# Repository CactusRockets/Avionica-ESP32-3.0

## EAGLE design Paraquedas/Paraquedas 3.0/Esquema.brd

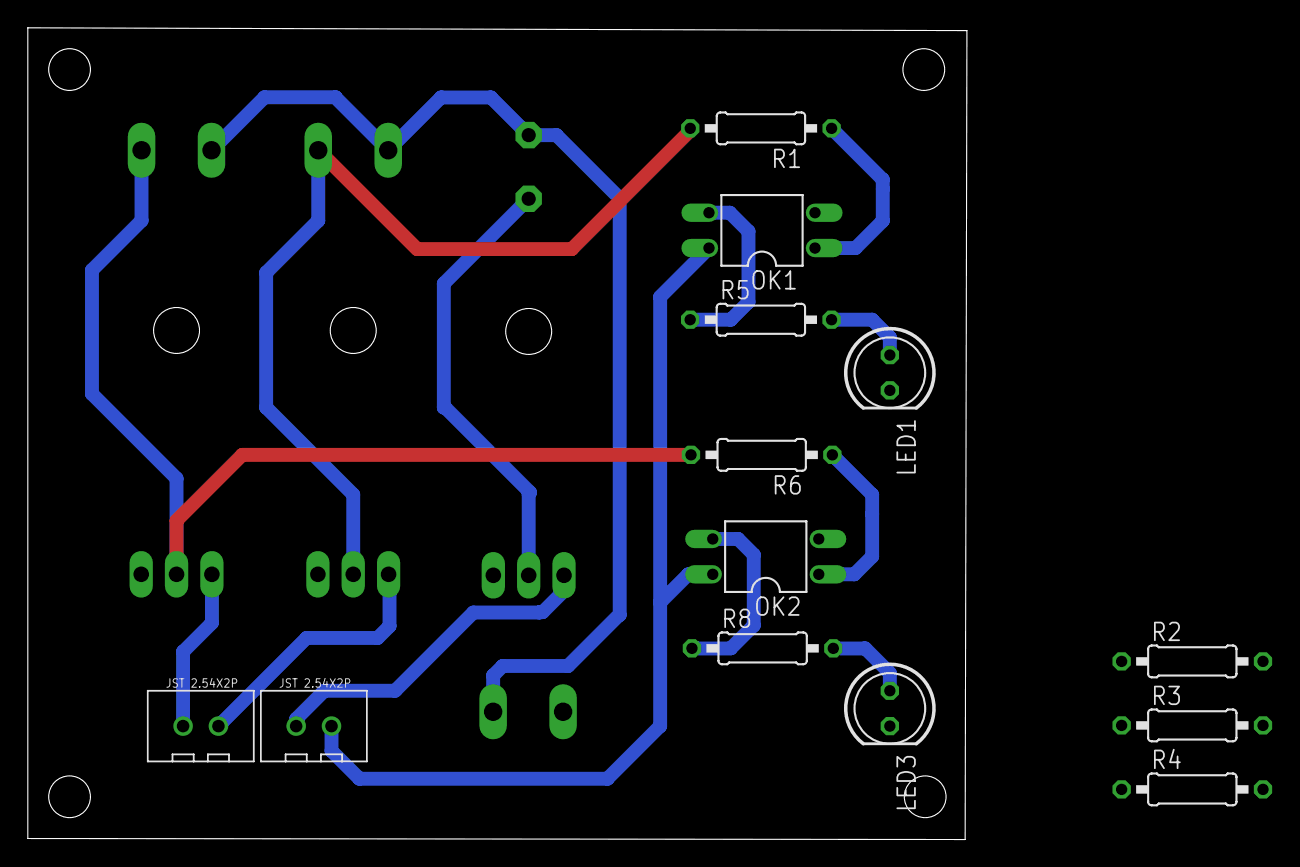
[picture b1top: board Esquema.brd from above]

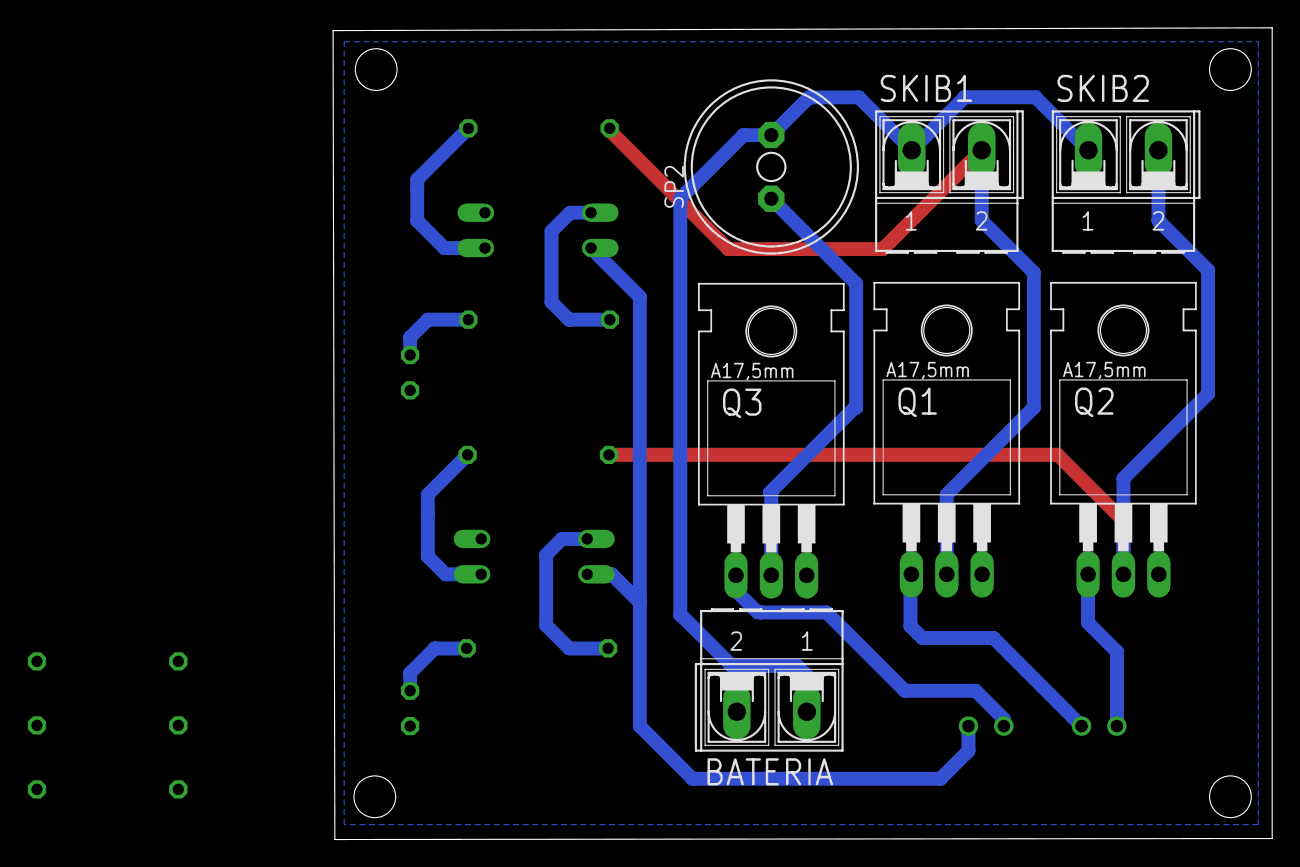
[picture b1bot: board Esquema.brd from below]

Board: 2 copper layers, 67.5 x 58.3 mm, 20 parts (7 on the bottom side), 15 nets.

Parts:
BATERIA: AK500/2-H
LED1, LED3: 5mm; LED5MM
OK1, OK2: PC817; DIL04
Q1, Q2, Q3: IRF540; TO220
R1, R5, R8: 220; 0207/10
R2, R3, R4, R6: 1k; 0207/10
SKIB1, SKIB2: AK500/2-H
SP2: AL11P
U$1, U$2: JST2.54X2P; JST2.54X2P_FOOTPRINT

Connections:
3.3V: OK1.4, OK2.4, U$1.2
BUZZER: Q3.1, U$1.1
GND: BATERIA.2, LED1.K, LED3.K, OK1.2, OK2.2, Q1.3, Q2.3, Q3.3
unnamed: Q3.2, SP2.-
unnamed: LED3.A, R8.2
unnamed: OK1.1, R1.1
unnamed: OK2.1, R6.1
unnamed: LED1.A, R5.2
SINAL_SKIB1: OK1.3, R5.1
SINAL_SKIB2: OK2.3, R8.1
SKIB1: Q1.1, U$2.2
SKIB1_CONECTOR: Q1.2, R1.2, SKIB1.2
SKIB2: Q2.1, U$2.1
SKIB2_CONECTOR: Q2.2, R6.2, SKIB2.2
VCC: BATERIA.1, SKIB1.1, SKIB2.1, SP2.+
